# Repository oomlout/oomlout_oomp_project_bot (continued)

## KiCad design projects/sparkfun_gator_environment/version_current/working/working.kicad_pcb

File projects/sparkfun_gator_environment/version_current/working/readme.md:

# gator_environment by sparkfun  
This is a harvested standardized copy of a project from github.  
The original project can be found at:  
https://github.com/sparkfun/gator_environment  
Please consult that link for additional, details, files, and license information.  
Note: It was auto harvested and if the original repo had more than one board file or anything out of the ordinary the files here are likely not representative.

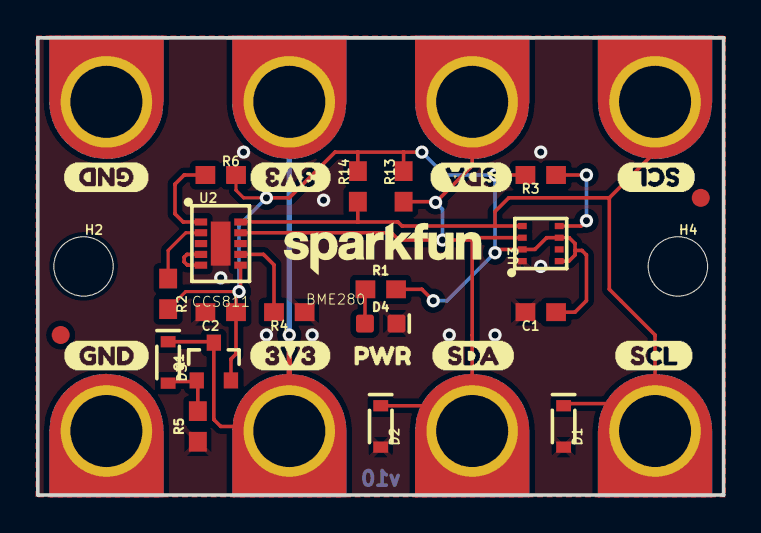
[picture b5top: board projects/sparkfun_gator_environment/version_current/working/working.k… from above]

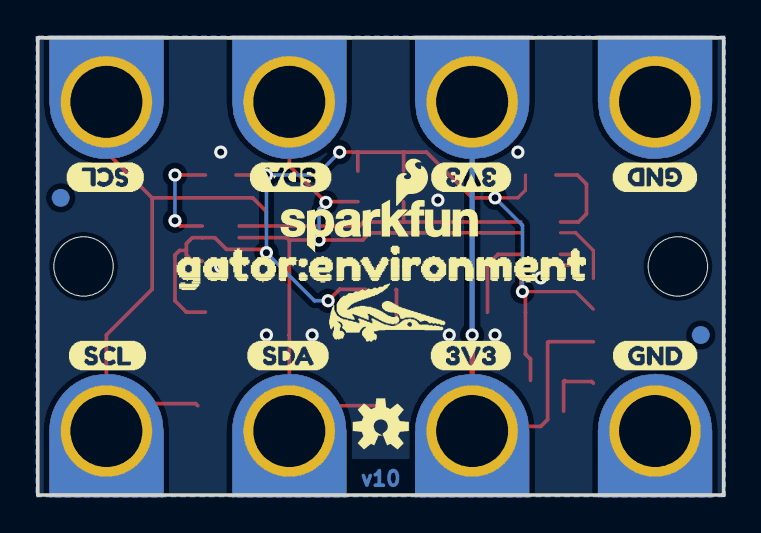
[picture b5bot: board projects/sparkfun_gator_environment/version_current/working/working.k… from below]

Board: 2 copper layers, 38.1 x 25.4 mm, 55 parts (14 on the bottom side), 12 nets.

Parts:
C1: 0.1uF; 0603
C2: 1.0uF; 0603
D1, D2, D3: 3.6V; SOD-323
D4: RED; LED-0603
FD1, FD2, FD3, FD4: FIDUCIAL1X2; FIDUCIAL-1X2
FRAME1: FRAME-LETTER; CREATIVE_COMMONS
H2, H4: STAND-OFF
J1, J2, J3, J4, J5, J6, J7, J8: GATORGATOR_MINI; GATOR_MINI
LOGO1: SFE_LOGO_NAME.1_INCH; SFE_LOGO_NAME_.1
LOGO2: SFE_LOGO_NAME_FLAME.1_INCH; SFE_LOGO_NAME_FLAME_.1
LOGO4: OSHW-LOGOS; OSHW-LOGO-S
Q1: 2.5A/30V/105mΩ; SOT23-3
R1: 1k; 0603
R2: 4.7k; 0603
R3, R4, R6: 100k; 0603
R5, R13, R14: 10k; 0603
U2: CCS811; LGA10
U3: BME280; LGA-8-2.5X2.5
U$1, U$8, U$16, U$21: 3V33
U$2, U$7, U$15, U$20: GND0
U$3, U$6, U$14, U$23: SCL2
U$4, U$5, U$13, U$22: SDA1
U$18: PWR0
U$19: GATORBIT_FINAL_FOR_SILK#01#PNG
U$24: ORDERING_INSTRUCTIONS
U$25: GATOR#ENVIRONMENT0

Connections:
3.3V: C1.1, C2.1, Q1.2, R1.2, R2.2, R3.2, R6.2, R13.2, R14.2, U2.6, U3.2, U3.6, U3.8
CCS811_ADDR: R6.1, U2.1
GND: C1.2, C2.2, D1.A, D2.A, D4.C, J4.P$2, J5.P$2, R4.1, R5.1, U2.EP, U3.1, U3.7
unnamed: D4.A, R1.1
unnamed: D3.C, J3.P$2, J6.P$2, Q1.3
unnamed: D3.A, Q1.1, R5.2
NTC_SENSE: U2.4, U2.5
SCL: D1.C, J1.P$2, J8.P$2, R14.1, U2.10, U3.4
SDA: D2.C, J2.P$2, J7.P$2, R13.1, U2.9, U3.3
SDO/ADR: R3.1, U3.5
~RST: R2.1, U2.2
~WAKE: R4.2, U2.7

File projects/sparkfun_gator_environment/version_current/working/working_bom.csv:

Row,Description,Part,References,Value,Footprint,Quantity Per PCB,Status,Datasheet
1,,0.1UF-0603-25V-(+80/-20%),C1,0.1UF-0603-25V-(+80/-20%),0603,1, ,
2,,1.0UF-0603-16V-10%,C2,1.0UF-0603-16V-10%,0603,1, ,
3,,DIODE-ZENER-BZT52C3V6S,D1 D2 D3,DIODE-ZENER-BZT52C3V6S,SOD-323,3, ,
4,,LED-RED0603,D4,RED,LED-0603,1, ,
5,,FRAME-LETTER,FRAME1,FRAME-LETTER,CREATIVE_COMMONS,1, ,
6,,STAND-OFF,H2 H4,STAND-OFF,STAND-OFF,2, ,
7,,GATORGATOR_MINI,J1 J2 J3 J4 J5 J6 J7 J8,GATORGATOR_MINI,GATOR_MINI,8, ,
8,,OSHW-LOGOS,LOGO4,OSHW-LOGOS,OSHW-LOGO-S,1, ,
9,,SFE_LOGO_NAME.1_INCH,LOGO1,SFE_LOGO_NAME.1_INCH,SFE_LOGO_NAME_.1,1, ,
10,,SFE_LOGO_NAME_FLAME.1_INCH,LOGO2,SFE_LOGO_NAME_FLAME.1_INCH,SFE_LOGO_NAME_FLAME_.1,1, ,
11,,MOSFET_PCH-DMG2307L,Q1,MOSFET_PCH-DMG2307L,SOT23-3,1, ,
12,,100KOHM-0603-1/10W-1%,R3 R4 R6,100KOHM-0603-1/10W-1%,0603,3, ,
13,,10KOHM-0603-1/10W-1%,R5 R13 R14,10KOHM-0603-1/10W-1%,0603,3, ,
14,,1KOHM-0603-1/10W-1%,R1,1KOHM-0603-1/10W-1%,0603,1, ,
15,,4.7KOHM-0603-1/10W-1%,R2,4.7KOHM-0603-1/10W-1%,0603,1, ,
16,,BME280,U3,BME280,LGA-8-2.5X2.5,1, ,
17,,CCS811PRODUCTION,U2,CCS811PRODUCTION,LGA10,1, ,





Project info:
Schematic:,working
Variant:,default
Revision:,
Date:,2023-08-06_12-56-02
KiCad Version:,7.0.6-7.0.6~ubuntu22.04.1
Statistics:
Component Groups:,17
Component Count:,31 (0 SMD/ 0 THT)
Fitted Components:,31 (0 SMD/ 0 THT)
Number of PCBs:,1
Total Components:,31

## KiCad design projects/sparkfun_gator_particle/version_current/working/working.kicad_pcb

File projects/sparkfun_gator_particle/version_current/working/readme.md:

# OOMP Project  
## gator_particle  by sparkfun  
  
oomp key: oomp_projects_flat_sparkfun_gator_particle  
(snippet of original readme)  
  
SparkFun gator:particle - micro:bit Accessory Board  
=============================  

[*SparkFun gator:particle - micro:bit Accessory Board (SEN-15271)*](https://www.sparkfun.com/products/15271)  
  
An I<sup>2</sup>C sensor for detecting particles. Additionaly, the MAX30102 sensor can also be used for measure heart-rate and SpO<sub>2</sub> using special algorithms. These algorithms have limited functionality and are primarily meant for demonstration purposed.  
  
*Example of pulse measurement:*  

Instead of using pin connections or requiring soldering, this product provides connection pads for a more kid freindly experience with alligator clips. The design intention of this product is to be used with the [gato:bit (v2)](https://www.sparkfun.com/products/15162), and the [micro:bit development board](https://www.sparkfun.com/products/14208).  
  
Repository Contents  
-------------------  
  
* **/Hardware** - Eagle design files (.brd, .sch)  
* **/Production** - Production panel files (.brd)  
  
Documentation  
--------------  
* **[Hookup Guide](https://learn.sparkfun.com/tutorials/sparkfun-gatorparticle-hookup-guide)** - Basic hookup guide for the gator:particle.  
* **[gator:particle PXT Package](https://github.com/sparkfun  
  full source readme at [readme_src.md](readme_src.md)  
  
source repo at: [https://github.com/sparkfun/gator_particle](https://github.com/sparkfun/gator_particle)  
## Board  

## Schematic  

[schematic pdf](working_schematic.pdf)  
## Images

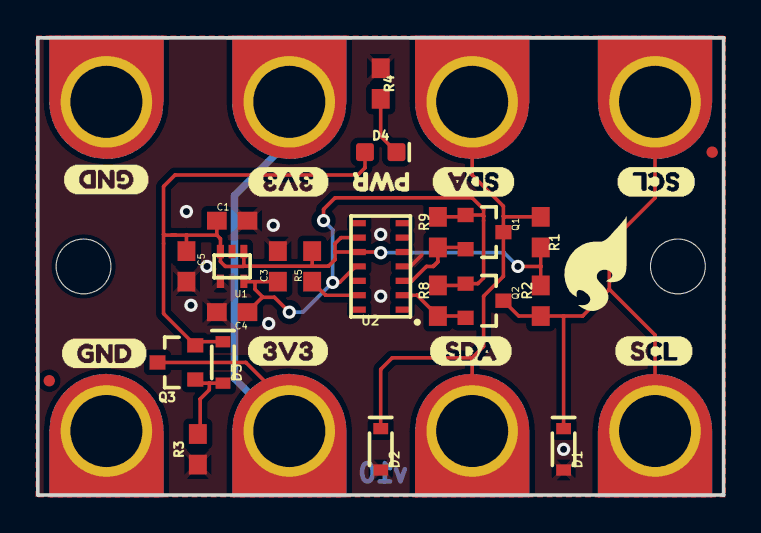
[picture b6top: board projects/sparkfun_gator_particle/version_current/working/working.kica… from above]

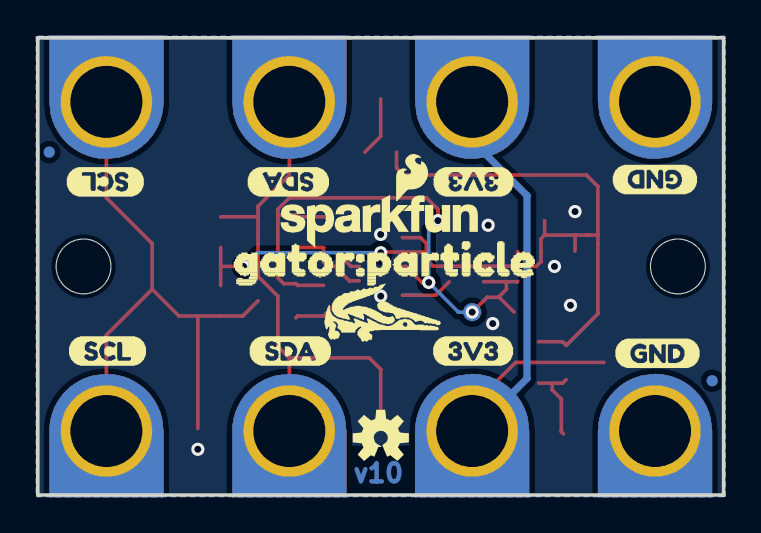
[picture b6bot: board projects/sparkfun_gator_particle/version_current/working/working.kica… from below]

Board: 2 copper layers, 38.1 x 25.4 mm, 59 parts (15 on the bottom side), 11 nets.

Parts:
C1, C3: 0.1uF; 0603
C4: 4.7uF; 0603
C5: 10uF; 0603
D1, D2, D3: 3.6V; SOD-323
D4: RED; LED-0603
FID1, FID2, FID3, FID4: FIDUCIALUFIDUCIAL; FIDUCIAL-MICRO
FRAME1: FRAME-LETTER; CREATIVE_COMMONS
J1, J2, J3, J4, J5, J6, J7, J8: GATORGATOR_MINI; GATOR_MINI
LOGO1: SFE_LOGO_NAME_FLAME.1_INCH; SFE_LOGO_NAME_FLAME_.1
LOGO2: OSHW-LOGOS; OSHW-LOGO-S
Q1, Q2: 220mA/50V/3.5Ω; SOT23-3
Q3: 2.5A/30V/105mΩ; SOT23-3
R1, R2, R3, R4: 10k; 0603
R5: 4.7k; 0603
R8, R9: 2.2k; 0603
STANDOFF2, STANDOFF3: STAND-OFFTIGHT; STAND-OFF-TIGHT
TP1: 1.8V Test; PAD.03X.04
U1: 1.8V/100mA; SC70
U2: 30102; OLGA-14
U$1, U$5, U$9, U$13: GND0
U$2, U$6, U$10, U$14: 3V33
U$3, U$7, U$11, U$15: SDA2
U$4, U$8, U$12, U$16: SCL1
U$17: SFE_LOGO_FLAME_.2
U$18: ORDERING_INSTRUCTIONS
U$19: PWR0
U$21: GATORBIT_FINAL_FOR_SILK#01#PNG
U$22: GATOR#PARTICLE0

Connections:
1.8V: C3.1, C4.1, Q1.1, Q2.1, R8.2, R9.2, TP1.P$1, U1.5, U2.11
3.3V: C1.1, C5.1, D3.C, D4.A, Q3.2, R1.2, R2.2, R5.2, U1.1, U1.3, U2.9, U2.10
GND: C1.2, C3.2, C4.2, C5.2, D1.A, D2.A, J1.P$2, J5.P$2, R3.1, R4.1, U1.2, U1.4, U2.4, U2.12
LV_SCL: Q2.2, R8.1, U2.2
LV_SDA: Q1.2, R9.1, U2.3
unnamed: D3.A, Q3.1, R3.2
unnamed: J2.P$2, J6.P$2, Q3.3
unnamed: D4.C, R4.2
SCL: D1.C, J4.P$2, J8.P$2, Q2.3, R2.1
SDA: D2.C, J3.P$2, J7.P$2, Q1.3, R1.1
~INT: R5.1, U2.13

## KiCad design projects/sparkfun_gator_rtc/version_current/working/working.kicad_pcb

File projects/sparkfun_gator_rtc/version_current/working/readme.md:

# OOMP Project  
## gator_rtc  by sparkfun  
  
oomp key: oomp_projects_flat_sparkfun_gator_rtc  
(snippet of original readme)  
  
SparkFun gator:RTC - micro:bit Accessory Board  
=============================  

[*SparkFun gator:RTC - micro:bit Accessory Board (COM-15486)*](https://www.sparkfun.com/products/15486)    
  
The gator:RTC is a supplemental data logging tool to be used in conjunction with the [gator:log](https://www.sparkfun.com/products/15270), part of SparkFun's gator:bit series of gator-clippable accessories designed for easy interface with the micro:bit or other microcontrollers. This tool allows a student to focus more on the experiment than watching a thermometer or stopwatch.  
  
Instead of using pin connections or requiring soldering, this product provides connection pads for a more kid freindly experience with alligator clips. The design intention of this product is to be used with the [gato:bit (v2)](https://www.sparkfun.com/products/15162), and the [micro:bit development board](https://www.sparkfun.com/products/14208).  
  
Repository Contents  
-------------------  
  
* **/Hardware** - Eagle design files (.brd, .sch)  
  
Documentation  
--------------  
  
* **[Hookup Guide](https://learn.sparkfun.com/tutorials/sparkfun-gatorrtc-hookup-guide)** - Basic hookup guide for the gator:RTC.  
* **[gator:RTC PXT Package](https://github.com/sparkfun/pxt-gator-rtc)** - PXT- package for the MakeCode gator:RTC extension.  
  
License Information  
-------------------  
  
Th  
  full source readme at [readme_src.md](readme_src.md)  
  
source repo at: [https://github.com/sparkfun/gator_rtc](https://github.com/sparkfun/gator_rtc)  
## Board  

## Schematic  

[schematic pdf](working_schematic.pdf)  
## Images

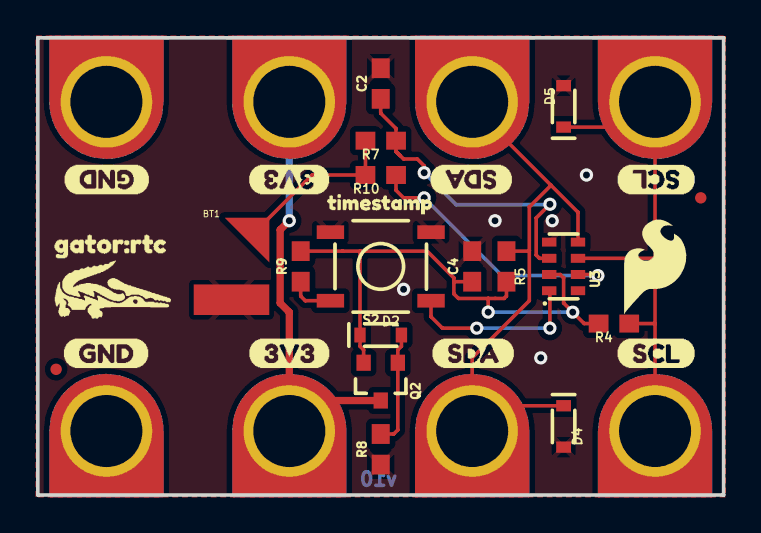
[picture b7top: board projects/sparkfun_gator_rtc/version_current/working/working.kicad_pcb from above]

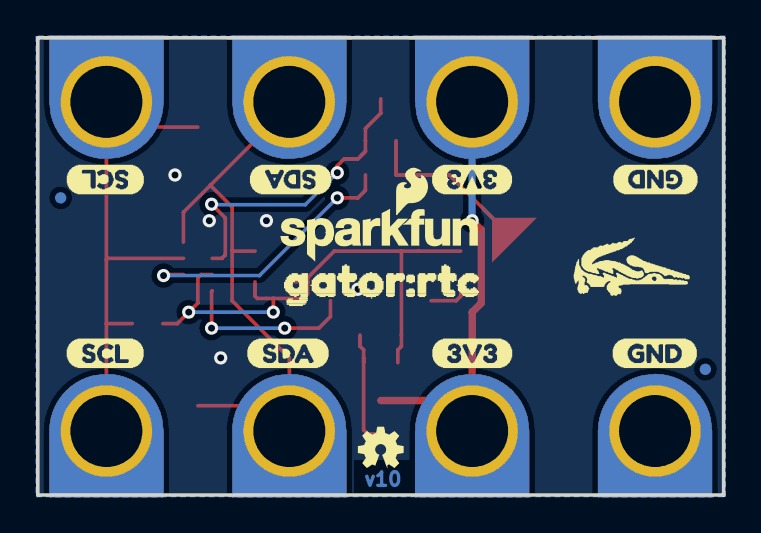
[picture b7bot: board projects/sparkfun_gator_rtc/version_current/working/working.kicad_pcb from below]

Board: 2 copper layers, 38.1 x 25.4 mm, 53 parts (14 on the bottom side), 10 nets.

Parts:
BT1: ML414H_IV01E_BATTERY; ML414H_IV01E
C2, C4: 0.1uF; 0603
D2, D4, D5: 3.6V; SOD-323
FID1, FID2, FID3, FID4: FIDUCIALUFIDUCIAL; FIDUCIAL-MICRO
FRAME1: FRAME-LETTER; CREATIVE_COMMONS
J2, J3, J4, J6, J7, J8, J9, J10: GATORGATOR_MINI; GATOR_MINI
LOGO2: OSHW-LOGOMINI; OSHW-LOGO-MINI
LOGO4: SFE_LOGO_NAME_FLAME.1_INCH; SFE_LOGO_NAME_FLAME_.1
Q2: 2.5A/30V/105mΩ; SOT23-3
R4, R5, R8, R9, R10: 10k; 0603
R7: 470; 0603
S2: TACTILE_SWITCH_SMD_5.2MM
U3: RV-3028
U$1, U$3, U$12, U$15: 3V33
U$2, U$10, U$11, U$23: GND0
U$4, U$7, U$13, U$16: SDA1
U$5, U$6, U$14, U$18: SCL2
U$8, U$21: GATORBIT_FINAL_FOR_SILK#01#PNG
U$9: SFE_LOGO_FLAME_.2
U$17: TIMESTAMP0
U$20, U$24: GATOR#RTC0
U$22: ORDERING_INSTRUCTIONS

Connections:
3.3V: C4.1, D2.C, Q2.2, R4.2, R5.2, R9.2, U3.7
GND: BT1.-, C2.2, C4.2, D4.A, D5.A, J6.P$2, J10.P$2, R8.1, S2.3, S2.4, U3.5
unnamed: J4.P$2, J9.P$2, Q2.3
unnamed: D2.A, Q2.1, R8.2
unnamed: R9.1, S2.1, S2.2, U3.8
SCL: D5.C, J2.P$2, J7.P$2, R4.1, U3.3
SDA: D4.C, J3.P$2, J8.P$2, R5.1, U3.4
VBACKUP: C2.1, R7.1, U3.6
V_BATT: BT1.+, R7.2, R10.2
~RST: R10.1, U3.2

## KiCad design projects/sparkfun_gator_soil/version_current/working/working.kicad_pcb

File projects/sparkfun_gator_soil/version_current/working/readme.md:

# gator_soil by sparkfun  
This is a harvested standardized copy of a project from github.  
The original project can be found at:  
https://github.com/sparkfun/gator_soil  
Please consult that link for additional, details, files, and license information.  
Note: It was auto harvested and if the original repo had more than one board file or anything out of the ordinary the files here are likely not representative.

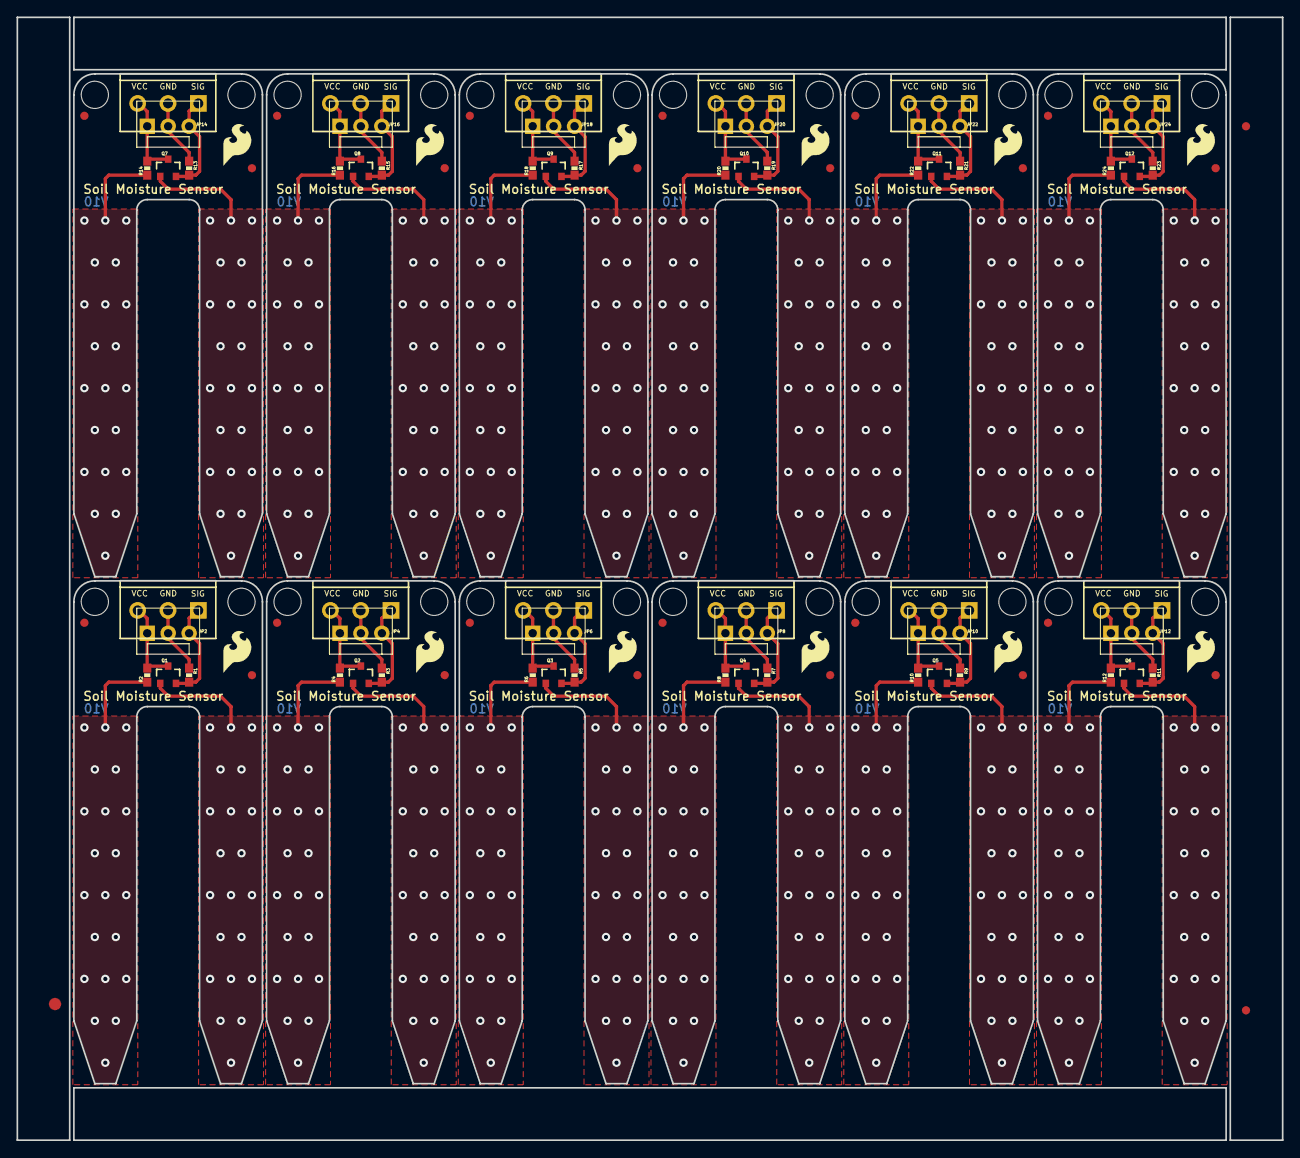
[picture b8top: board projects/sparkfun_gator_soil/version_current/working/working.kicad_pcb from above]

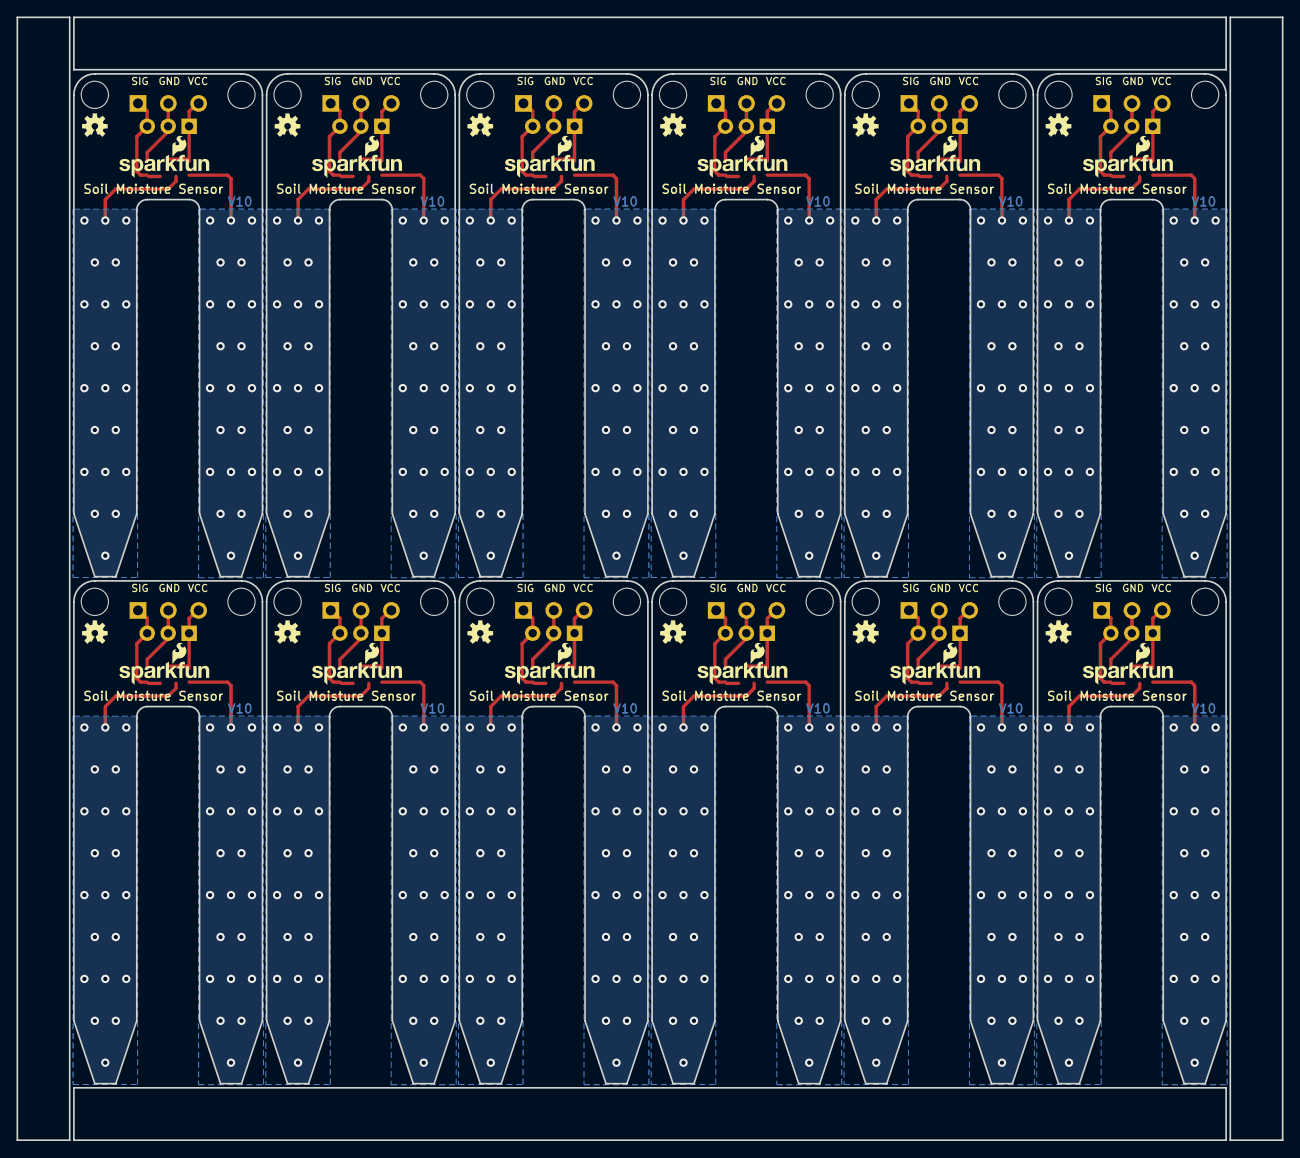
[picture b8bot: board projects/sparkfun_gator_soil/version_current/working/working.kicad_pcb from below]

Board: 2 copper layers, 153.4 x 136.1 mm, 147 parts (24 on the bottom side), 36 nets.

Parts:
E$1: FIDUCIAL-1.5X3
E$4, E$5: FIDUCIAL-1X2
FID1, FID2, FID3, FID4, FID5, FID6, FID7, FID8, FID9, FID10, FID11, FID12, FID13, FID14, FID15, FID16, FID17, FID18, FID19, FID20, FID21, FID22, FID23, FID24: FIDUCIAL1X2; FIDUCIAL-1X2
JP1, JP3, JP5, JP7, JP9, JP11, JP13, JP15, JP17, JP19, JP21, JP23: DNP; MOLEX-1X3
JP2, JP4, JP6, JP8, JP10, JP12, JP14, JP16, JP18, JP20, JP22, JP24: SCREWTERMINAL-3.5MM-3_LOCK.007S
LOGO1, LOGO3, LOGO5, LOGO7, LOGO9, LOGO11, LOGO13, LOGO15, LOGO17, LOGO19, LOGO21, LOGO23: SFE_LOGO_NAME_FLAME.1_INCH; SFE_LOGO_NAME_FLAME_.1
LOGO2, LOGO4, LOGO6, LOGO8, LOGO10, LOGO12, LOGO14, LOGO16, LOGO18, LOGO20, LOGO22, LOGO24: OSHW-LOGOS; OSHW-LOGO-S
Q1, Q2, Q3, Q4, Q5, Q6, Q7, Q8, Q9, Q10, Q11, Q12: 2N3904; SOT23-3
R1, R3, R5, R7, R9, R11, R13, R15, R17, R19, R21, R23: 10k; 0603-RES
R2, R4, R6, R8, R10, R12, R14, R16, R18, R20, R22, R24: 100; 0603-RES
STANDOFF1, STANDOFF2, STANDOFF3, STANDOFF4, STANDOFF5, STANDOFF6, STANDOFF7, STANDOFF8, STANDOFF9, STANDOFF10, STANDOFF11, STANDOFF12, STANDOFF13, STANDOFF14, STANDOFF15, STANDOFF16, STANDOFF17, STANDOFF18, STANDOFF19, STANDOFF20, STANDOFF21, STANDOFF22, STANDOFF23, STANDOFF24: STAND-OFF
U$1, U$2, U$3, U$4, U$5, U$6, U$7, U$8, U$9, U$10, U$11, U$12: SFE_LOGO_FLAME_.2

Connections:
GND: JP1.2, JP2.2, R1.1
GND1: JP3.2, JP4.2, R3.1
GND2: JP5.2, JP6.2, R5.1
GND3: JP7.2, JP8.2, R7.1
GND4: JP9.2, JP10.2, R9.1
GND5: JP11.2, JP12.2, R11.1
GND6: JP13.2, JP14.2, R13.1
GND7: JP15.2, JP16.2, R15.1
GND8: JP17.2, JP18.2, R17.1
GND9: JP19.2, JP20.2, R19.1
GND10: JP21.2, JP22.2, R21.1
GND11: JP23.2, JP24.2, R23.1
SIG: JP1.3, JP2.1, Q1.2, R1.2
SIG1: JP3.3, JP4.1, Q2.2, R3.2
SIG2: JP5.3, JP6.1, Q3.2, R5.2
SIG3: JP7.3, JP8.1, Q4.2, R7.2
SIG4: JP9.3, JP10.1, Q5.2, R9.2
SIG5: JP11.3, JP12.1, Q6.2, R11.2
SIG6: JP13.3, JP14.1, Q7.2, R13.2
SIG7: JP15.3, JP16.1, Q8.2, R15.2
SIG8: JP17.3, JP18.1, Q9.2, R17.2
SIG9: JP19.3, JP20.1, Q10.2, R19.2
SIG10: JP21.3, JP22.1, Q11.2, R21.2
SIG11: JP23.3, JP24.1, Q12.2, R23.2
VCC: JP1.1, JP2.3, Q1.3, R2.2
VCC1: JP3.1, JP4.3, Q2.3, R4.2
VCC2: JP5.1, JP6.3, Q3.3, R6.2
VCC3: JP7.1, JP8.3, Q4.3, R8.2
VCC4: JP9.1, JP10.3, Q5.3, R10.2
VCC5: JP11.1, JP12.3, Q6.3, R12.2
VCC6: JP13.1, JP14.3, Q7.3, R14.2
VCC7: JP15.1, JP16.3, Q8.3, R16.2
VCC8: JP17.1, JP18.3, Q9.3, R18.2
VCC9: JP19.1, JP20.3, Q10.3, R20.2
VCC10: JP21.1, JP22.3, Q11.3, R22.2
VCC11: JP23.1, JP24.3, Q12.3, R24.2
